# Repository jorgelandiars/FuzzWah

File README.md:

# FuzzWah8Tr
Pedal Fuzz-Wah de 8 transistores

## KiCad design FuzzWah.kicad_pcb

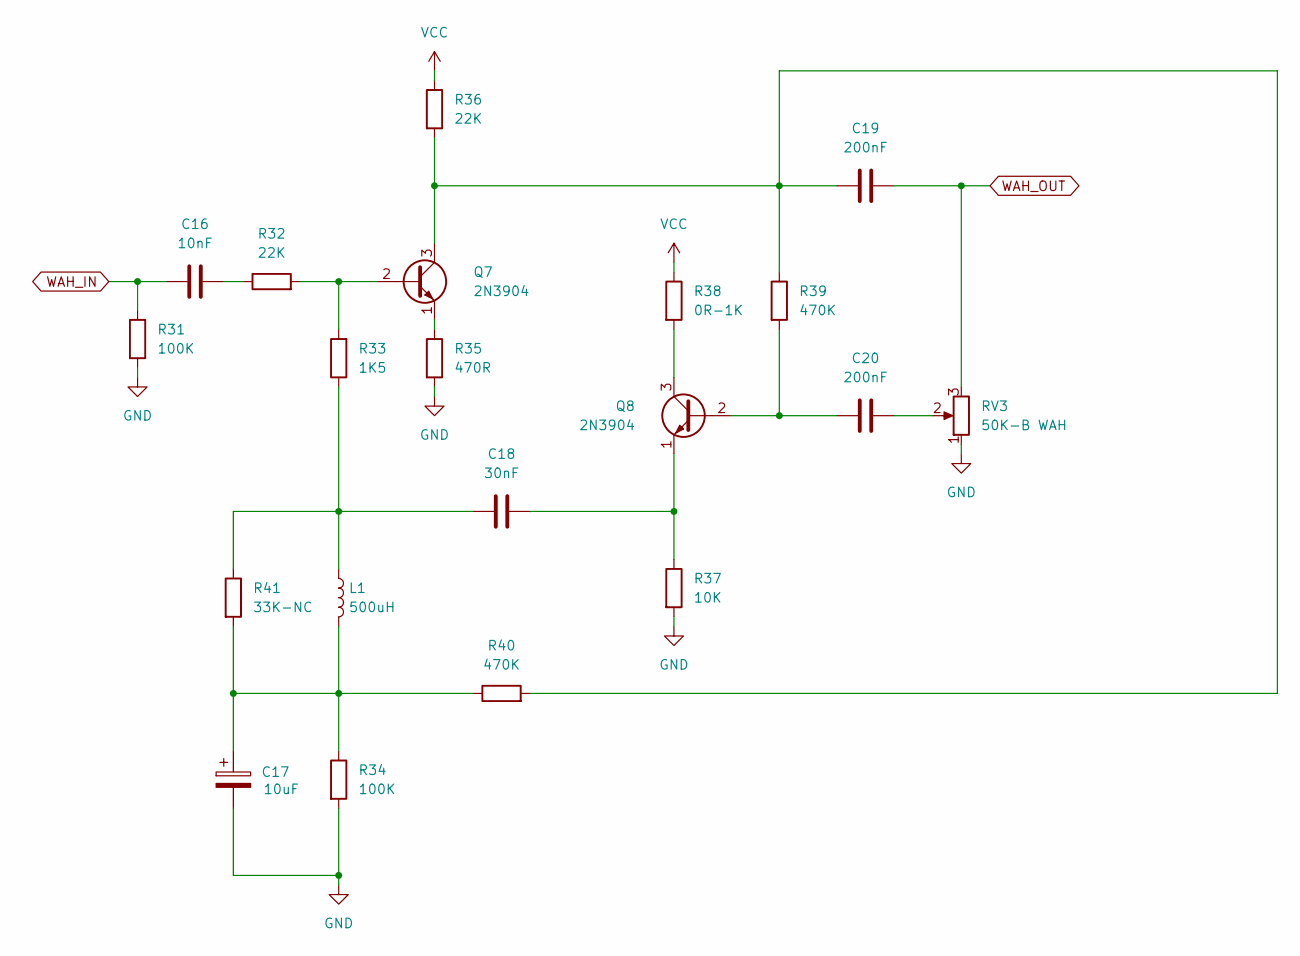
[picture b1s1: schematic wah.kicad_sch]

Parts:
C16: 10nF; C_Disc_D5.1mm_W3.2mm_P5.00mm
C17: 10uF; CP_Radial_D5.0mm_P2.00mm
C18: 30nF; C_Disc_D5.1mm_W3.2mm_P5.00mm
C19, C20: 200nF; C_Disc_D5.1mm_W3.2mm_P5.00mm
L1: 500uH; L_Radial_D7.2mm_P3.00mm_Murata_1700
Q7, Q8: 2N3904; TO-92_Inline
R31, R34: 100K; R_Axial_DIN0207_L6.3mm_D2.5mm_P7.62mm_Horizontal
R32, R36: 22K; R_Axial_DIN0207_L6.3mm_D2.5mm_P7.62mm_Horizontal
R33: 1K5; R_Axial_DIN0207_L6.3mm_D2.5mm_P7.62mm_Horizontal
R35: 470R; R_Axial_DIN0207_L6.3mm_D2.5mm_P7.62mm_Horizontal
R37: 10K; R_Axial_DIN0207_L6.3mm_D2.5mm_P7.62mm_Horizontal
R38: 0R-1K; R_Axial_DIN0207_L6.3mm_D2.5mm_P7.62mm_Horizontal
R39, R40: 470K; R_Axial_DIN0207_L6.3mm_D2.5mm_P7.62mm_Horizontal
R41: 33K-NC; R_Axial_DIN0207_L6.3mm_D2.5mm_P7.62mm_Horizontal
RV3: 50K-B WAH; Pot Alpha 16mm

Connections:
GND: C17.2, R31.2, R34.2, R35.2, R37.2, RV3.1; also elsewhere on the board
unnamed: C16.2, R32.1
unnamed: C17.1, L1.2, R34.1, R40.1, R41.2
unnamed: C18.1, L1.1, R33.1, R41.1
unnamed: C20.2, RV3.2
unnamed: Q7.2 (B), R32.2, R33.2
unnamed: C19.2, Q7.3 (C), R36.2, R39.1, R40.2
unnamed: Q7.1 (E), R35.1
unnamed: C20.1, Q8.2 (B), R39.2
unnamed: Q8.3 (C), R38.2
unnamed: C18.2, Q8.1 (E), R37.1
VCC: R36.1, R38.1; also elsewhere on the board
WAH_IN: C16.1, R31.1; also elsewhere on the board
WAH_OUT: C19.1, RV3.3; also elsewhere on the board

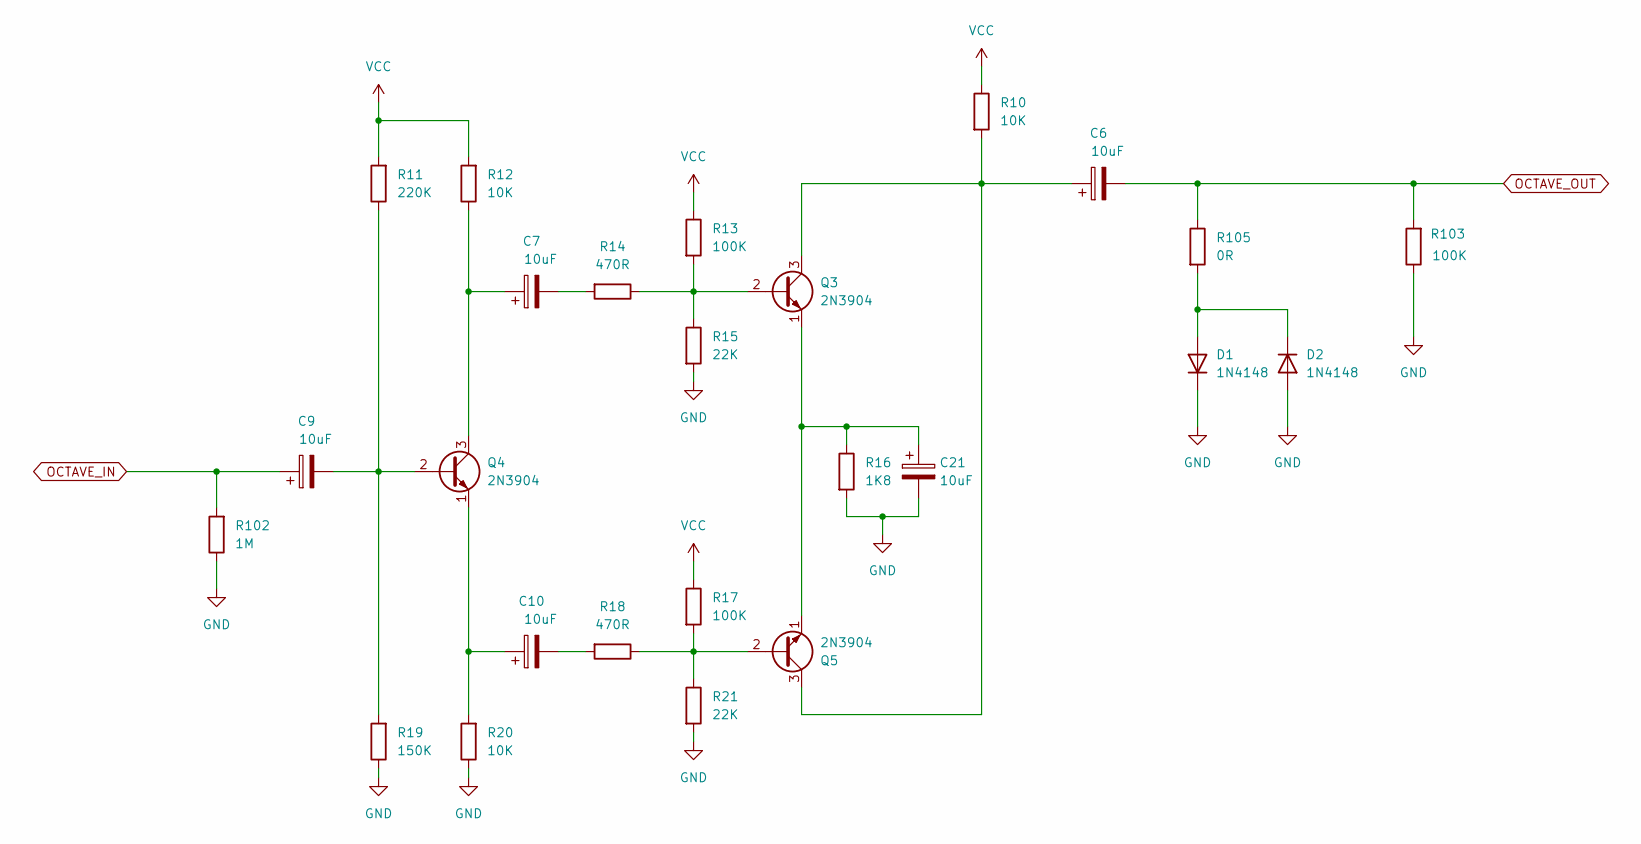
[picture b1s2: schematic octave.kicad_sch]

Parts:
C6, C7, C9, C10, C21: 10uF; CP_Radial_D5.0mm_P2.00mm
D1, D2: 1N4148; D_DO-35_SOD27_P7.62mm_Horizontal
Q3, Q4, Q5: 2N3904; TO-92_Inline
R10, R12, R20: 10K; R_Axial_DIN0207_L6.3mm_D2.5mm_P7.62mm_Horizontal
R11: 220K; R_Axial_DIN0207_L6.3mm_D2.5mm_P7.62mm_Horizontal
R13, R17, R103: 100K; R_Axial_DIN0207_L6.3mm_D2.5mm_P7.62mm_Horizontal
R14, R18: 470R; R_Axial_DIN0207_L6.3mm_D2.5mm_P7.62mm_Horizontal
R15, R21: 22K; R_Axial_DIN0207_L6.3mm_D2.5mm_P7.62mm_Horizontal
R16: 1K8; R_Axial_DIN0207_L6.3mm_D2.5mm_P7.62mm_Horizontal
R19: 150K; R_Axial_DIN0207_L6.3mm_D2.5mm_P7.62mm_Horizontal
R102: 1M; R_Axial_DIN0207_L6.3mm_D2.5mm_P7.62mm_Horizontal
R105: 0R; R_Axial_DIN0207_L6.3mm_D2.5mm_P7.62mm_Horizontal

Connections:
GND: C21.2, D1.1 (K), D2.2 (A), R15.2, R16.2, R19.1, R20.1, R21.2, R102.1, R103.1; also elsewhere on the board
unnamed: C7.2, R14.2
unnamed: C10.2, R18.2
unnamed: D1.2 (A), D2.1 (K), R105.2
unnamed: Q3.2 (B), R13.2, R14.1, R15.1
unnamed: C6.1, Q3.3 (C), Q5.3 (C), R10.2
unnamed: C21.1, Q3.1 (E), Q5.1 (E), R16.1
unnamed: C9.2, Q4.2 (B), R11.1, R19.2
unnamed: C7.1, Q4.3 (C), R12.1
unnamed: C10.1, Q4.1 (E), R20.2
unnamed: Q5.2 (B), R17.2, R18.1, R21.1
OCTAVE_IN: C9.1, R102.2; also elsewhere on the board
OCTAVE_OUT: C6.2, R103.2, R105.1; also elsewhere on the board
VCC: R10.1, R11.2, R12.2, R13.1, R17.1; also elsewhere on the board

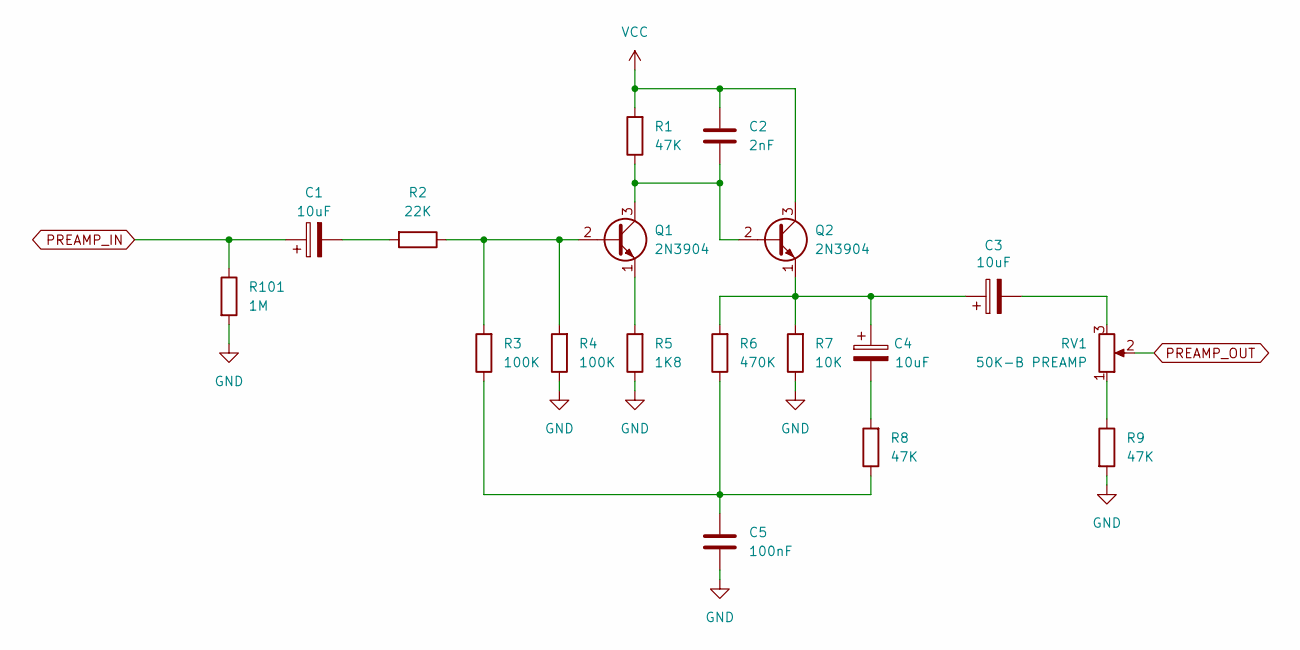
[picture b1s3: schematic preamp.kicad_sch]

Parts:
C1, C3, C4: 10uF; CP_Radial_D5.0mm_P2.00mm
C2: 2nF; C_Disc_D5.1mm_W3.2mm_P5.00mm
C5: 100nF; C_Disc_D5.1mm_W3.2mm_P5.00mm
Q1, Q2: 2N3904; TO-92_Inline
R1, R8, R9: 47K; R_Axial_DIN0207_L6.3mm_D2.5mm_P7.62mm_Horizontal
R2: 22K; R_Axial_DIN0207_L6.3mm_D2.5mm_P7.62mm_Horizontal
R3, R4: 100K; R_Axial_DIN0207_L6.3mm_D2.5mm_P7.62mm_Horizontal
R5: 1K8; R_Axial_DIN0207_L6.3mm_D2.5mm_P7.62mm_Horizontal
R6: 470K; R_Axial_DIN0207_L6.3mm_D2.5mm_P7.62mm_Horizontal
R7: 10K; R_Axial_DIN0207_L6.3mm_D2.5mm_P7.62mm_Horizontal
R101: 1M; R_Axial_DIN0207_L6.3mm_D2.5mm_P7.62mm_Horizontal
RV1: 50K-B PREAMP; Pot Alpha 16mm

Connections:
GND: C5.2, R4.1, R5.1, R7.1, R9.2, R101.2; also elsewhere on the board
unnamed: C1.2, R2.2
unnamed: C3.2, RV1.3
unnamed: C4.2, R8.2
unnamed: C5.1, R3.1, R6.1, R8.1
unnamed: Q1.2 (B), R2.1, R3.2, R4.2
unnamed: C2.2, Q1.3 (C), Q2.2 (B), R1.1
unnamed: Q1.1 (E), R5.2
unnamed: C3.1, C4.1, Q2.1 (E), R6.2, R7.2
unnamed: R9.1, RV1.1
PREAMP_IN: C1.1, R101.1; also elsewhere on the board
PREAMP_OUT: RV1.2; also elsewhere on the board
VCC: C2.1, Q2.3 (C), R1.2; also elsewhere on the board

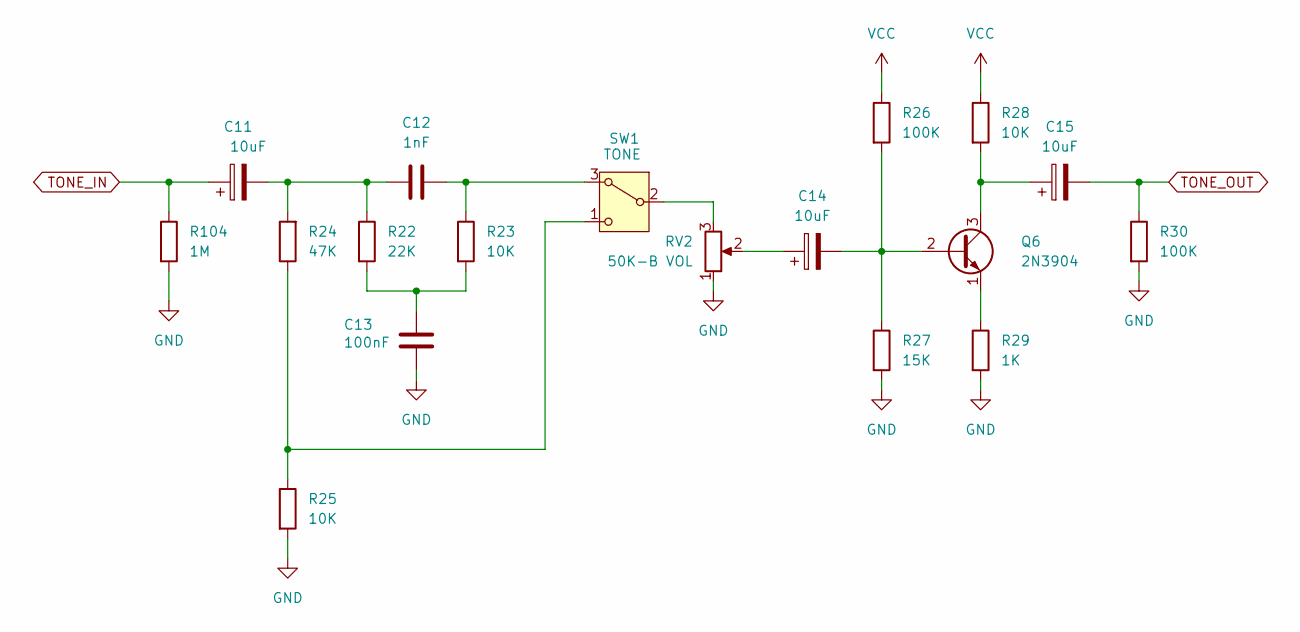
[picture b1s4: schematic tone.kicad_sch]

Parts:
C11, C14, C15: 10uF; CP_Radial_D5.0mm_P2.00mm
C12: 1nF; C_Disc_D5.1mm_W3.2mm_P5.00mm
C13: 100nF; C_Disc_D5.1mm_W3.2mm_P5.00mm
Q6: 2N3904; TO-92_Inline
R22: 22K; R_Axial_DIN0207_L6.3mm_D2.5mm_P7.62mm_Horizontal
R23, R25, R28: 10K; R_Axial_DIN0207_L6.3mm_D2.5mm_P7.62mm_Horizontal
R24: 47K; R_Axial_DIN0207_L6.3mm_D2.5mm_P7.62mm_Horizontal
R26, R30: 100K; R_Axial_DIN0207_L6.3mm_D2.5mm_P7.62mm_Horizontal
R27: 15K; R_Axial_DIN0207_L6.3mm_D2.5mm_P7.62mm_Horizontal
R29: 1K; R_Axial_DIN0207_L6.3mm_D2.5mm_P7.62mm_Horizontal
R104: 1M; R_Axial_DIN0207_L6.3mm_D2.5mm_P7.62mm_Horizontal
RV2: 50K-B VOL; Pot Alpha 16mm
SW1: TONE; SW_SPDT_V2

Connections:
GND: C13.2, R25.2, R27.2, R29.2, R30.2, R104.2, RV2.1; also elsewhere on the board
unnamed: C11.2, C12.1, R22.1, R24.2
unnamed: C13.1, R22.2, R23.2
unnamed: C14.1, RV2.2
unnamed: C14.2, Q6.2 (B), R26.2, R27.1
unnamed: C15.1, Q6.3 (C), R28.2
unnamed: Q6.1 (E), R29.1
unnamed: C12.2, R23.1, SW1.3 (A)
unnamed: RV2.3, SW1.2 (B)
unnamed: R24.1, R25.1, SW1.1 (C)
TONE_IN: C11.1, R104.1; also elsewhere on the board
TONE_OUT: C15.2, R30.1; also elsewhere on the board
VCC: R26.1, R28.1; also elsewhere on the board

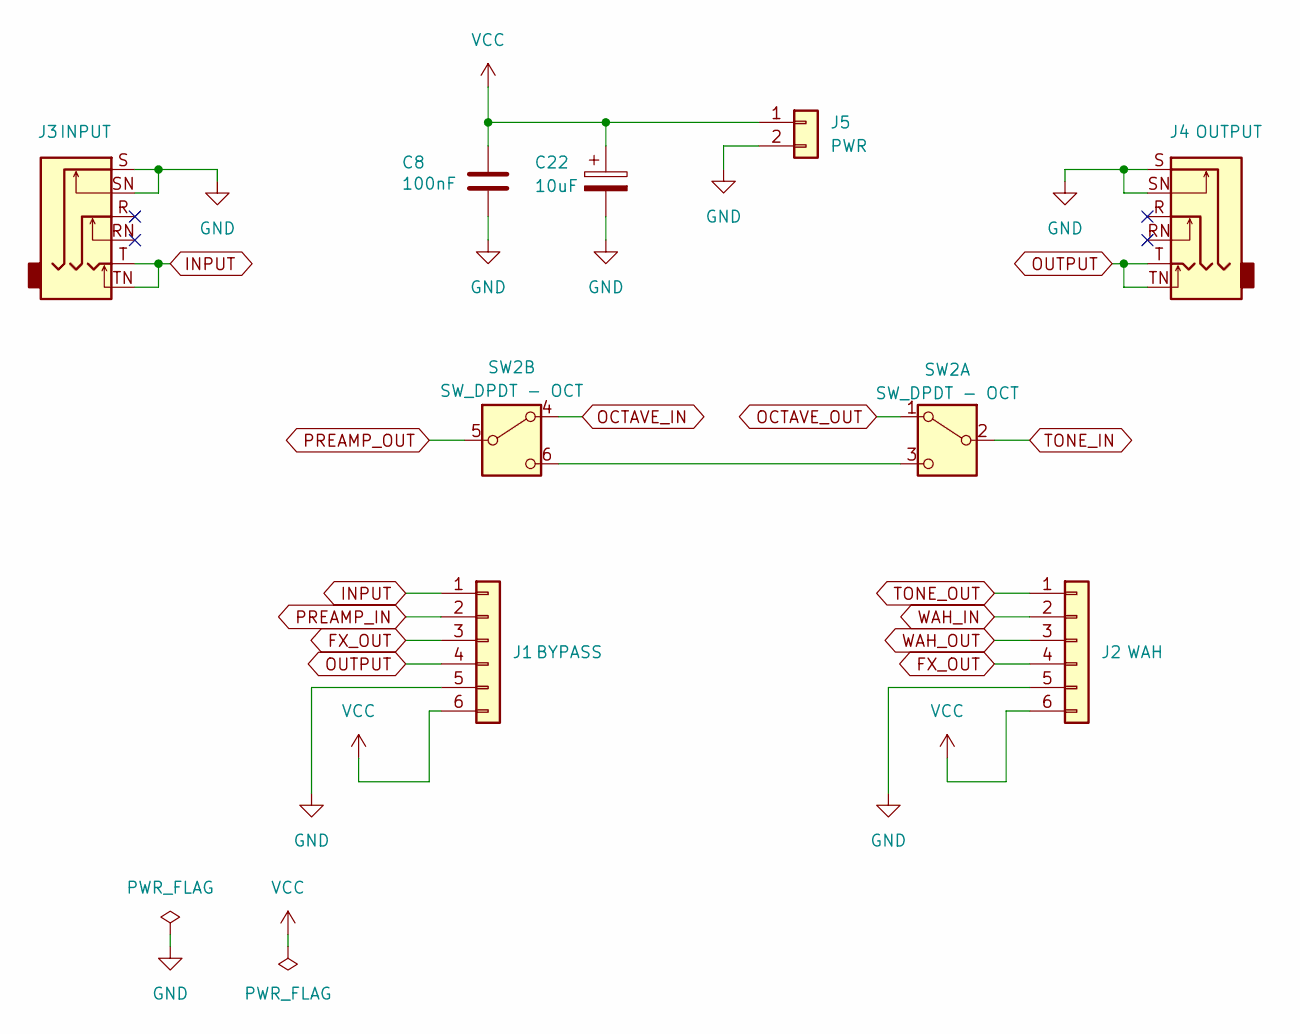
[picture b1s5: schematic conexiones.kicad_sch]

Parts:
C8: 100nF; C_Disc_D5.1mm_W3.2mm_P5.00mm
C22: 10uF; CP_Radial_D5.0mm_P2.00mm
J1: BYPASS; PinHeader_1x06_P2.54mm_Vertical
J2: WAH; PinHeader_1x06_P2.54mm_Vertical
J3: INPUT; Jack_6.35mm_Neutrik_NMJ6HCD3_Horizontal
J4: OUTPUT; Jack_6.35mm_Neutrik_NMJ6HCD3_Horizontal
J5: PWR; PinHeader_1x02_P2.54mm_Vertical
SW2: SW_DPDT - OCT; SW_DPDT

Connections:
FX_OUT: J1.3, J2.4
GND: C8.2, C22.2, J1.5, J2.5, J3.S, J3.SN, J4.S, J4.SN, J5.2; also elsewhere on the board
INPUT: J1.1, J3.T, J3.TN
unnamed: SW2.3 (C), SW2.6 (C)
OCTAVE_IN: SW2.4 (A); also elsewhere on the board
OCTAVE_OUT: SW2.1 (A); also elsewhere on the board
OUTPUT: J1.4, J4.T, J4.TN
PREAMP_IN: J1.2; also elsewhere on the board
PREAMP_OUT: SW2.5 (B); also elsewhere on the board
TONE_IN: SW2.2 (B); also elsewhere on the board
TONE_OUT: J2.1; also elsewhere on the board
VCC: C8.1, C22.1, J1.6, J2.6, J5.1; also elsewhere on the board
WAH_IN: J2.2; also elsewhere on the board
WAH_OUT: J2.3; also elsewhere on the board

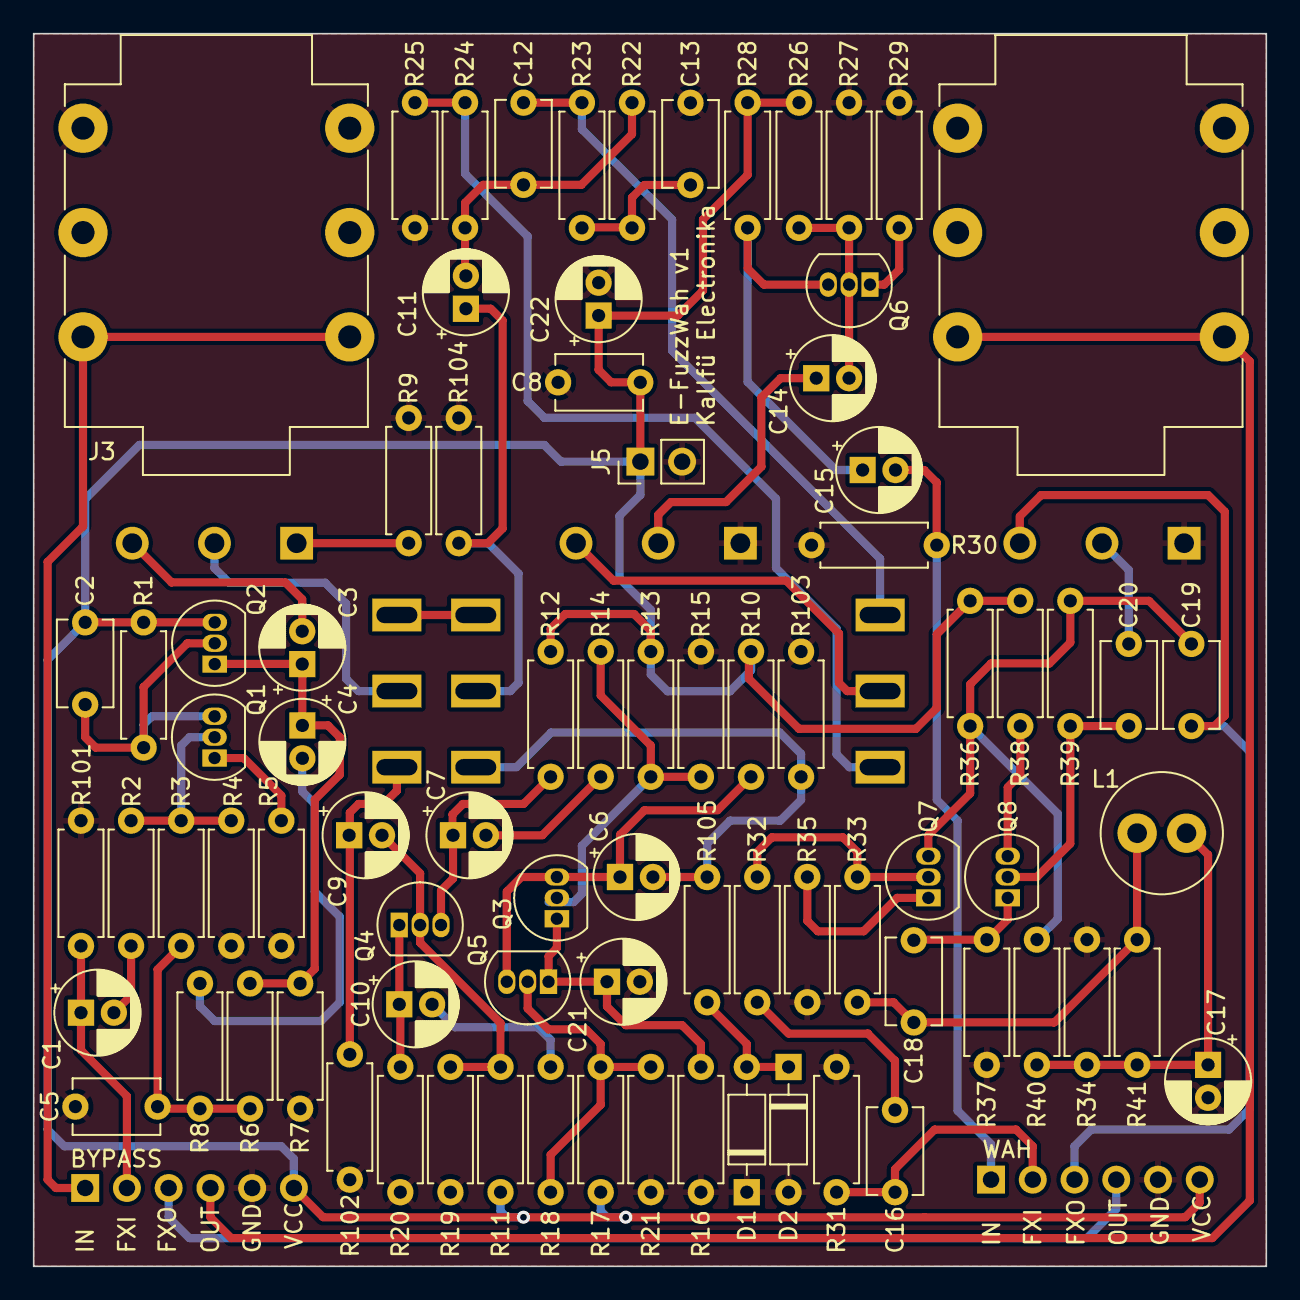
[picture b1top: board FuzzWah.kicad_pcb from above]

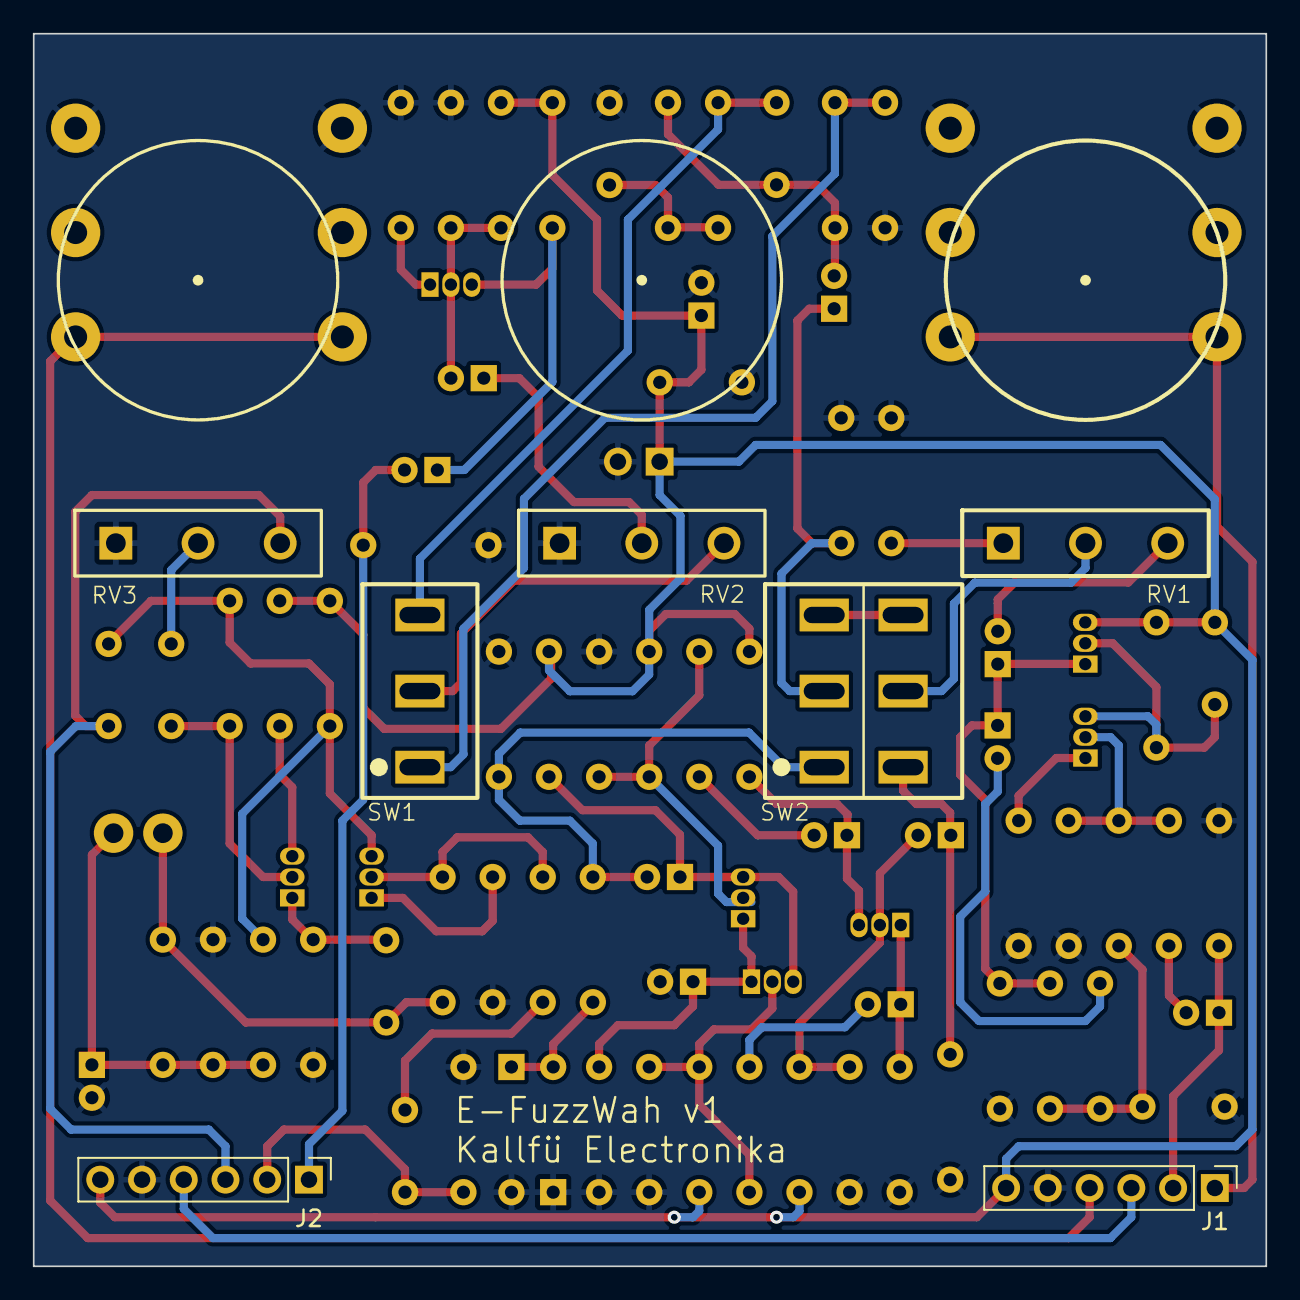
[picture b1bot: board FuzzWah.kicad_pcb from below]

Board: 2 copper layers, 75.0 x 75.0 mm, 89 parts (7 on the bottom side), 52 nets.

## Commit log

2025-02-14 Primer commit
2025-02-14 Añadir .gitignore para KiCad
2025-03-06 Actualización de esquemáticos
2025-03-14 Actualización esquemáticos
2025-03-16 Asignación de huellas a componentes.
2025-03-19 Adctualización de PCB
2025-04-02 Finalización de PCB (archivos fabricación pendientes)
2025-04-03 Archivos de Fabricación listos.
2025-04-03 Finalización Archivos de Fabricación FuzzWah v1.
